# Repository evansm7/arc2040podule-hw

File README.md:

# RP2040-based Acorn Archimedes expansion card

22nd October 2021

This is a design for an expansion card (or "Podule" in Acorn-words) for the Acorn Archimedes computer.  Instead of the traditional EPROMs and 74-series logic, or PALs, this card uses the Raspberry Pi RP2040 microcontroller to interface directly to the expansion card bus.

This allows the functionality of the podule to be largely software-defined in the RP2040 firmware.

The card comprises 5V-3.3V buffering, the MCU, QSPI flash and crystal, and a USB micro-B device port for both programming the MCU and communicating with it when in action.

In conjunction with the [arc2040podule firmware](https://github.com/evansm7/arc2040podule), this podule provides a source of boot-time loaded Relocatable Modules (up to ~2MB, or ~8MB with large SPI flash fitted!) and a USB comms link with a host computer which can be used for file transfer, networking, etc.

**This is a work in progress!**  Board v1 was simply an experiment to prove the basic operation.  See below: v1 required extensive modifications to function, so _please do not build V1_.

Yes, it's sort of overkill to have two 133MHz processors providing IO for an 8MHz processor, but that's 2021 vs 1987 for you.  The RP2040 is ideal for this task because one core can be dedicated to the realtime bitbanging Arc bus cycles, with the other core dealing with comms and providing the peripheral model.

## Features

  * Raspberry Pi RP2040 microcontroller
  * Software-defined presentation to Archimedes
  * 4KB of expansion address space
  * Supports up to 8MB QSPI flash; almost all is free for ROM modules 
  * Supports open-collector IRQ and reset of the Archimedes
  * USB interface to a host computer (reflash, comms)
  * Debug blinky LED
  * SWD header
  * Reset button
  * BOOT button next to the Reset button for awkward, but possible, one-handed programming-reboot
  * Spare GPIO pins to a header
  * Micro-SD connector via SPI

## Principle of operation

The expansion card bus (and control signals) pass through 74AVLC164245 16-bit bus transceivers, which interface the 5V Arc to the 3.3V MCU.  The lower 8 bits of data are bidirectional, and the direction of the lower byte of the transceiver `IC3` is controlled by the `PR/nW` podule bus signal (called `PRNW` here).

The RP2040 polls the `/IORD` and `/IOWR` strobes, `/PS` podule select line, and address lines.  When a strobe falls, the RP2040 emulates the corresponding read or write cycle by presenting/capturing data on the `D[7:0]` data bus.

All address lines, `LA[13:2]`, are presented to the RP2040, permitting the full 16KB region to be decoded.

This podule only supports IOC cycles.  The `/IORQ` & `/IOGT` signals are not connected, due to lack of free GPIO pins.

Similarly, the RP2040 doesn't have enough GPIO pins to support a 16-bit data bus, so we deal with 8.

The good news is this podule is verified to perform synchronous (and slow) accesses correctly (v1 with hacks below, see notes).  Fast accesses have not been tested yet.

The RP2040 circuit is unremarkable and largely follows the RP design guide.  The BOOT signal is brought to a switch, which (on reset) conveniently brings the RP2040 up in USB MSD programming mode.

Browse the [schematic](doc/podule_2040_sch.pdf) and [board layout](doc/podule_2040_sch.pdf).

# Change log

## v2:

Changes from v1:

  * All points/v1 problems below have been resolved (but crystal still on bottom).
  * One more GPIO available (removed `NRST_I`).  GPIO header now brings out 4x GPIOs, 3.3V and ground.
  * Micro-SD footprint using GPIOs (corresponding to SPI1 pins).

**v2 has not been validated yet**  Boards are on their way.

## v1:

Requested changes (AKA a critique/lessons learned/mistakes in v1):

  * There's a fair bit of clown routing on v1 (late night, rushing to bundle this PCB off with another, regular excuses apply).  Clean routing.
   * Make net widths more consistent, e.g. some power nets change, and some are inconsistent either side of a component.
  * The QSPI routing is bad, and the decoupling is bad.  Fix both.
  * 74AVLC164245s are more easily available in TSSOP.  Change from SOP.
  * Add footprint for DNF pullup on flash `/CS`
  * 3.3V LDO is in an inconvenient/less common package.  Change for one of the cheap/plentiful packages (e.g. SOIC8)
  * Remove the `NRST_I` net input:  I found a software reset handshake is easier/more useful than polling for hardware reset.  This then frees a valuable single GPIO, for...
  * ...Add DNF SD footprint as an experimental option on 3x spare GPIOs (retain 0.1" header too).  Use newly-acquired spare GPIO for `/CS`.
  * Bring out USB Vbus to a link, or diode to 5V/LDO.  This would permit the board to be flashed while the host Arc is off, or unplugged.
  * Replace Y1 crystal footprint with a more common/available crystal.  (See notes.)
  * Move crystal to same side as MCU.
  * Decoupling:  Ensure 1x 0.1uF per power pin, even closer.  Caps closer to vias.  Add 0.1uF to QSPI flash.
  * Make address lines contiguous:  software _can_ juggle them, but it's a pain (and slows down the max cycle time).
  * _Crucially important_: Add 33Ω series termination on lines between the GPIO pins and the '245s.  See notes.
  * Wire both BOOT and RESET to a 4-pin header, for extension to 2 external buttons (e.g. outside the case of the Arc).

### Notes/observations on v1

I built the pictured prototype v1 with a 2MB QSPI flash, W25Q16JVSNIQ.  The flash doesn't work properly:  it only works slow, and I couldn't get 4-bit mode running.  Suspect decoupling & routing.

Ringing on the address lines hit a high voltage (~4V) and upset the RP2040.  This was a pain to find.  This manifest as USB stopping working while the Archimedes was powered on, yet working perfectly when it was off.  Adding 33Ω series termination on the address lines fixed this: add footprints on all control/data lines too (can always populate with 0Ω if it creates a problem).

The RP2040 design guide example uses a crystal with:
 
  * 27pF caps
  * 1K resistor
  * Crystal having 50 ohm ESR and 18pF load capacitance

The design guide says load cap should be (C1*C2)/(C1+C2)+parasitic, which (as caps are equal) simplifies to (C1/2)+parasitic.
Choose 5pF for parasitic and:  5+27/2 = 18.5, so choose 18pF crystal.

A similar worked example at: <https://suntsu.com/engineering-services/suntsu-application-notes/crystal-load-capacitance/>

Crystals in a 4-pin package (as used in v1) with 50 ohms and 18pF are uncommon.  For v1 I bodged on an 18pF 50ohm crystal (in wrong package -- Mouser 729-F91200084), and used 27pF caps.  Worked well.

Investigate more commonly-available packages, e.g. 4-pin but 3.2x2.5 instead of 5x3.2.

# Licence

This work is copyright 2021 Matt Evans, and is licenced under the Creative Commons CC BY-SA 3.0 license.

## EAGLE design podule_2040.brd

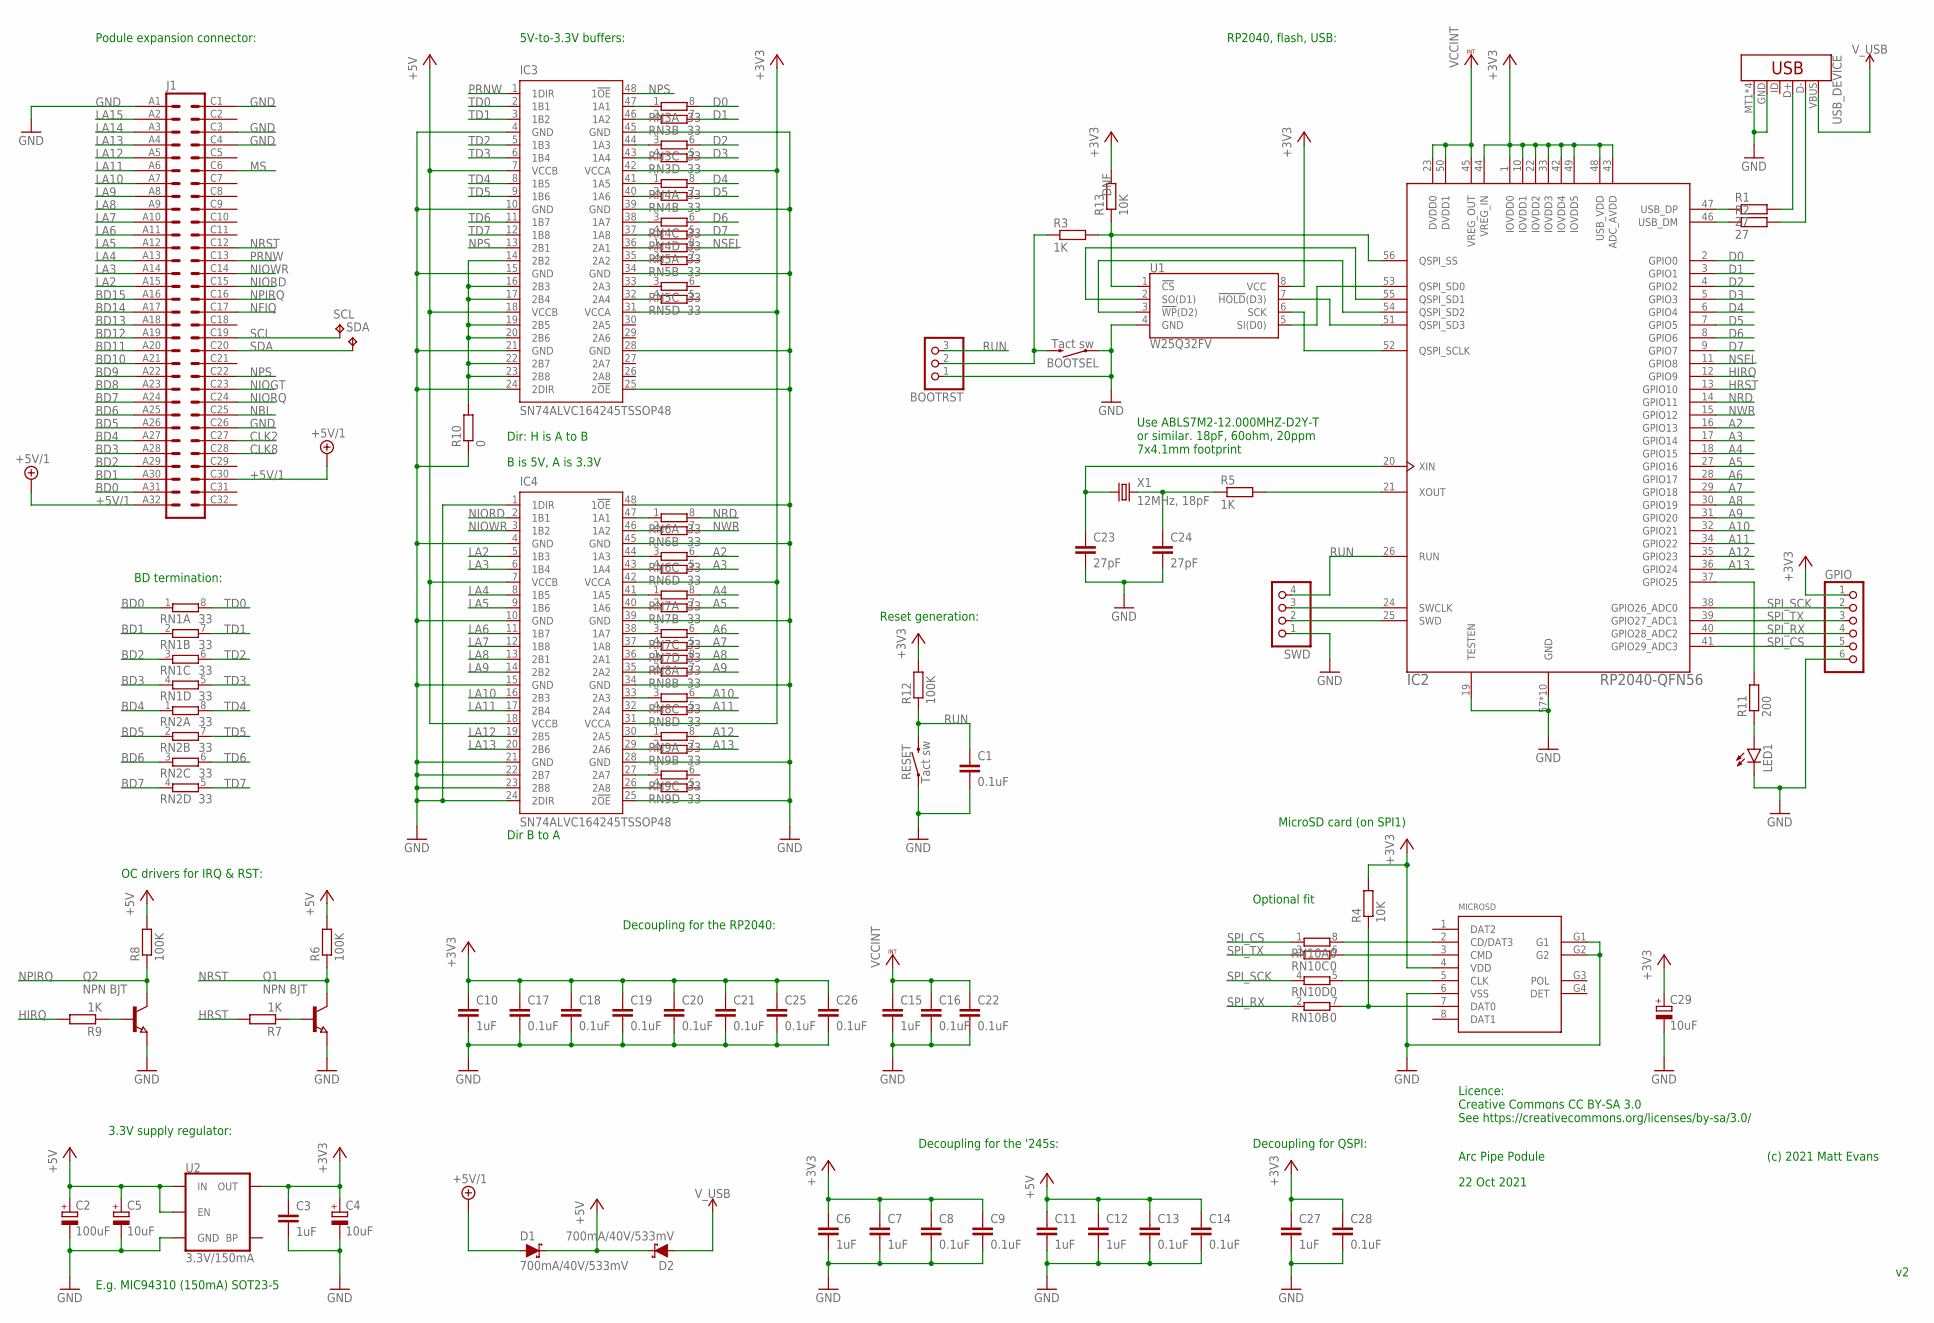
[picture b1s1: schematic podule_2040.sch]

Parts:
BOOTRST: PINHD-1X3; 1X03
BOOTSEL: Tact sw; TACTILE_SWITCH_SMD_5.2MM
C1, C8, C9, C13, C14, C16, C17, C18, C19, C20, C21, C22, C25, C26, C28: 0.1uF; C0603K
C2: 100uF; CT6032
C3, C6, C7, C10, C11, C12, C15, C27: 1uF; C0603K
C4, C5, C29: 10uF; A/3216-18W
C23, C24: 27pF; C0603K
D1, D2: 700mA/40V/533mV; SOT23-3
GPIO: PINHD-1X6; 1X06
IC2: RP2040-QFN56; RP2040-QFN-56
IC3, IC4: SN74ALVC164245TSSOP48; TSSOP48
J1: VG64SHORT; VG64KB-80MM
LED1: LEDCHIPLED_1206; CHIPLED_1206
MICROSD: MOLEX-USD-47309
Q1, Q2: NPN BJT; SOT23
R1, R2: 27; R0805
R3, R5, R7, R9: 1K; R0805
R4, R13: 10K; R0805
R6, R8, R12: 100K; R0805
R10: 0; R0603
R11: 200; R0805
RESET: Tact sw; TACTILE_SWITCH_SMD_5.2MM
RN1, RN2, RN3, RN4, RN5, RN6, RN7, RN8, RN9: 33; 0603-ARC
RN10: 0; 0603-ARC
SCL: TPTP15R; TP15R
SDA: TPTP15R; TP15R
SWD: PINHD-1X4; 1X04
U1: W25Q32FV; SOIC-8
U2: 3.3V/150mA; SOT23-5
USB_DEVICE: USB_MICRO-B_SMT; USB-MICROB
X1: 12MHz, 18pF; 7.5X5-2-PAD

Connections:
+3V3: C3.1, C4.+, C6.1, C7.1, C8.1, C9.1, C10.1, C17.1, C18.1, C19.1, C20.1, C21.1, C25.1, C26.1, C27.1, C28.1, C29.+, GPIO.1, IC2.1 (IOVDD0), IC2.10 (IOVDD1), IC2.22 (IOVDD2), IC2.33 (IOVDD3), IC2.42 (IOVDD4), IC2.43 (ADC_AVDD), IC2.44 (VREG_IN), IC2.48 (USB_VDD), IC2.49 (IOVDD5), IC3.31 (VCCA), IC3.42 (VCCA), IC4.31 (VCCA), IC4.42 (VCCA), MICROSD.4 (VDD), R4.2, R12.2, R13.2, U1.8 (VCC), U2.5 (OUT)
+5V: C2.+, C5.+, C11.1, C12.1, C13.1, C14.1, D1.3 (C), D2.3 (C), IC3.7 (VCCB), IC3.18 (VCCB), IC4.7 (VCCB), IC4.18 (VCCB), R6.2, R8.2, U2.1 (IN), U2.3 (EN)
+5V/1: D1.1 (A), J1.A32, J1.C30
A2: IC2.16 (GPIO13), RN6.6 (2)
A3: IC2.17 (GPIO14), RN6.5 (2)
A4: IC2.18 (GPIO15), RN7.8 (2)
A5: IC2.27 (GPIO16), RN7.7 (2)
A6: IC2.28 (GPIO17), RN7.6 (2)
A7: IC2.29 (GPIO18), RN7.5 (2)
A8: IC2.30 (GPIO19), RN8.8 (2)
A9: IC2.31 (GPIO20), RN8.7 (2)
A10: IC2.32 (GPIO21), RN8.6 (2)
A11: IC2.34 (GPIO22), RN8.5 (2)
A12: IC2.35 (GPIO23), RN9.8 (2)
A13: IC2.36 (GPIO24), RN9.7 (2)
BD0: J1.A31, RN1.1
BD1: J1.A30, RN1.2 (1)
BD2: J1.A29, RN1.3 (1)
BD3: J1.A28, RN1.4 (1)
BD4: J1.A27, RN2.1
BD5: J1.A26, RN2.2 (1)
BD6: J1.A25, RN2.3 (1)
BD7: J1.A24, RN2.4 (1)
BD8: J1.A23
BD9: J1.A22
BD10: J1.A21
BD11: J1.A20
BD12: J1.A19
BD13: J1.A18
BD14: J1.A17
BD15: J1.A16
CLK2: J1.C27
CLK8: J1.C28
D0: IC2.2 (GPIO0), RN3.8 (2)
D1: IC2.3 (GPIO1), RN3.7 (2)
D2: IC2.4 (GPIO2), RN3.6 (2)
D3: IC2.5 (GPIO3), RN3.5 (2)
D4: IC2.6 (GPIO4), RN4.8 (2)
D5: IC2.7 (GPIO5), RN4.7 (2)
D6: IC2.8 (GPIO6), RN4.6 (2)
D7: IC2.9 (GPIO7), RN4.5 (2)
GND: BOOTRST.1, BOOTSEL.1, BOOTSEL.2 (1), C1.2, C2.-, C3.2, C4.-, C5.-, C6.2, C7.2, C8.2, C9.2, C10.2, C11.2, C12.2, C13.2, C14.2, C15.2, C16.2, C17.2, C18.2, C19.2, C20.2, C21.2, C22.2, C23.2, C24.2, C25.2, C26.2, C27.2, C28.2, C29.-, GPIO.6, IC2.19 (TESTEN), IC2.57 (GND), IC2.58 (GND), IC2.59 (GND), IC2.60 (GND), IC2.61 (GND), IC2.62 (GND), IC2.63 (GND), IC2.64 (GND), IC2.65 (GND), IC2.66 (GND), IC3.4 (GND), IC3.10 (GND), IC3.15 (GND), IC3.21 (GND), IC3.24 (2DIR), IC3.25 (2!OE), IC3.28 (GND), IC3.34 (GND), IC3.39 (GND), IC3.45 (GND), IC4.1 (1DIR), IC4.4 (GND), IC4.10 (GND), IC4.15 (GND), IC4.21 (GND), IC4.22 (2B7), IC4.23 (2B8), IC4.24 (2DIR), IC4.25 (2!OE), IC4.28 (GND), IC4.34 (GND), IC4.39 (GND), IC4.45 (GND), IC4.48 (1!OE), J1.A1, J1.C1, J1.C3, J1.C4, J1.C26, LED1.C, MICROSD.6 (VSS), MICROSD.G1, MICROSD.G2, Q1.2 (E), Q2.2 (E), R10.1, RESET.1, RESET.2 (1), SWD.1, U1.4 (GND), U2.2 (GND), USB_DEVICE.GND, USB_DEVICE.MT1 (SHIELD), USB_DEVICE.MT2 (SHIELD), USB_DEVICE.P$1 (SHIELD), USB_DEVICE.P$2 (SHIELD)
HIRQ: IC2.12 (GPIO9), R9.2
HRST: IC2.13 (GPIO10), R7.2
LA2: IC4.5 (1B3), J1.A15
LA3: IC4.6 (1B4), J1.A14
LA4: IC4.8 (1B5), J1.A13
LA5: IC4.9 (1B6), J1.A12
LA6: IC4.11 (1B7), J1.A11
LA7: IC4.12 (1B8), J1.A10
LA8: IC4.13 (2B1), J1.A9
LA9: IC4.14 (2B2), J1.A8
LA10: IC4.16 (2B3), J1.A7
LA11: IC4.17 (2B4), J1.A6
LA12: IC4.19 (2B5), J1.A5
LA13: IC4.20 (2B6), J1.A4
LA14: J1.A3
LA15: J1.A2
MS: J1.C6
unnamed: IC2.47 (USB_DP), R1.1
unnamed: IC2.46 (USB_DM), R2.1
unnamed: R1.2, USB_DEVICE.D+
unnamed: R2.2, USB_DEVICE.D-
unnamed: IC2.52 (QSPI_SCLK), U1.6 (SCK)
unnamed: IC2.53 (QSPI_SD0), U1.5 (SI(D0))
unnamed: IC2.51 (QSPI_SD3), U1.7 (!HOLD!(D3))
unnamed: IC2.54 (QSPI_SD2), U1.3 (!WP!(D2))
unnamed: IC2.55 (QSPI_SD1), U1.2 (SO(D1))
unnamed: MICROSD.5 (CLK), RN10.5 (2)
unnamed: IC2.56 (QSPI_SS), R3.2, R13.1, U1.1 (!CS!)
unnamed: BOOTRST.2, BOOTSEL.3 (2), BOOTSEL.4 (2), R3.1
unnamed: IC2.21 (XOUT), R5.2
unnamed: MICROSD.2 (CD/DAT3), RN10.8 (2)
unnamed: IC2.25 (SWD), SWD.2
unnamed: IC2.24 (SWCLK), SWD.3
unnamed: C24.1, R5.1, X1.2
unnamed: Q1.1 (B), R7.1
unnamed: C23.1, IC2.20 (XIN), X1.1
unnamed: Q2.1 (B), R9.1
unnamed: IC3.47 (1A1), RN3.1
unnamed: IC3.14 (2B2), IC3.16 (2B3), IC3.17 (2B4), IC3.19 (2B5), IC3.20 (2B6), IC3.22 (2B7), IC3.23 (2B8), R10.2
unnamed: MICROSD.3 (CMD), RN10.6 (2)
unnamed: MICROSD.7 (DAT0), R4.1, RN10.7 (2)
unnamed: LED1.A, R11.1
unnamed: IC3.46 (1A2), RN3.2 (1)
unnamed: IC2.37 (GPIO25), R11.2
unnamed: IC3.32 (2A4), RN5.4 (1)
unnamed: IC3.44 (1A3), RN3.3 (1)
unnamed: IC3.43 (1A4), RN3.4 (1)
unnamed: IC3.40 (1A6), RN4.2 (1)
unnamed: IC3.41 (1A5), RN4.1
unnamed: IC3.38 (1A7), RN4.3 (1)
unnamed: IC3.37 (1A8), RN4.4 (1)
unnamed: IC3.36 (2A1), RN5.1
unnamed: IC3.35 (2A2), RN5.2 (1)
unnamed: IC3.33 (2A3), RN5.3 (1)
unnamed: IC4.47 (1A1), RN6.1
unnamed: IC4.46 (1A2), RN6.2 (1)
unnamed: IC4.44 (1A3), RN6.3 (1)
unnamed: IC4.43 (1A4), RN6.4 (1)
unnamed: IC4.41 (1A5), RN7.1
unnamed: IC4.40 (1A6), RN7.2 (1)
unnamed: IC4.38 (1A7), RN7.3 (1)
unnamed: IC4.37 (1A8), RN7.4 (1)
unnamed: IC4.36 (2A1), RN8.1
unnamed: IC4.35 (2A2), RN8.2 (1)
unnamed: IC4.33 (2A3), RN8.3 (1)
unnamed: IC4.32 (2A4), RN8.4 (1)
unnamed: IC4.30 (2A5), RN9.1
unnamed: IC4.29 (2A6), RN9.2 (1)
unnamed: IC4.27 (2A7), RN9.3 (1)
unnamed: IC4.26 (2A8), RN9.4 (1)
NBL: J1.C25
NFIQ: J1.C17
NIOGT: J1.C23
NIORD: IC4.2 (1B1), J1.C15
NIORQ: J1.C24
NIOWR: IC4.3 (1B2), J1.C14
NPIRQ: J1.C16, Q2.3 (C), R8.1
NPS: IC3.13 (2B1), IC3.48 (1!OE), J1.C22
NRD: IC2.14 (GPIO11), RN6.8 (2)
NRST: J1.C12, Q1.3 (C), R6.1
NSEL: IC2.11 (GPIO8), RN5.8 (2)
NWR: IC2.15 (GPIO12), RN6.7 (2)
PRNW: IC3.1 (1DIR), J1.C13
RUN: BOOTRST.3, C1.1, IC2.26 (RUN), R12.1, RESET.3 (2), RESET.4 (2), SWD.4
SCL: J1.C19, SCL.TP
SDA: J1.C20, SDA.TP
SPI_CS: GPIO.5, IC2.41 (GPIO29_ADC3), RN10.1
SPI_RX: GPIO.4, IC2.40 (GPIO28_ADC2), RN10.2 (1)
SPI_SCK: GPIO.2, IC2.38 (GPIO26_ADC0), RN10.4 (1)
SPI_TX: GPIO.3, IC2.39 (GPIO27_ADC1), RN10.3 (1)
TD0: IC3.2 (1B1), RN1.8 (2)
TD1: IC3.3 (1B2), RN1.7 (2)
TD2: IC3.5 (1B3), RN1.6 (2)
TD3: IC3.6 (1B4), RN1.5 (2)
TD4: IC3.8 (1B5), RN2.8 (2)
TD5: IC3.9 (1B6), RN2.7 (2)
TD6: IC3.11 (1B7), RN2.6 (2)
TD7: IC3.12 (1B8), RN2.5 (2)
VCCINT: C15.1, C16.1, C22.1, IC2.23 (DVDD0), IC2.45 (VREG_OUT), IC2.50 (DVDD1)
V_USB: D2.1 (A), USB_DEVICE.VBUS

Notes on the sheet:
B is 5V, A is 3.3V
Dir: H is A to B
Dir B to A
Podule expansion connector:
5V-to-3.3V buffers:
BD termination:
OC drivers for IRQ & RST:
3.3V supply regulator:
Decoupling for the '245s:
RP2040, flash, USB:
Arc Pipe Podule
(c) 2021 Matt Evans
22 Oct 2021
Licence: Creative Commons CC BY-SA 3.0 See https://creativecommons.org/licenses/by-sa/3.0/
E.g. MIC94310 (150mA) SOT23-5
Use ABLS7M2-12.000MHZ-D2Y-T or similar. 18pF, 60ohm, 20ppm 7x4.1mm footprint
Decoupling for the RP2040:
Reset generation:
Decoupling for QSPI:
Optional fit
MicroSD card (on SPI1)

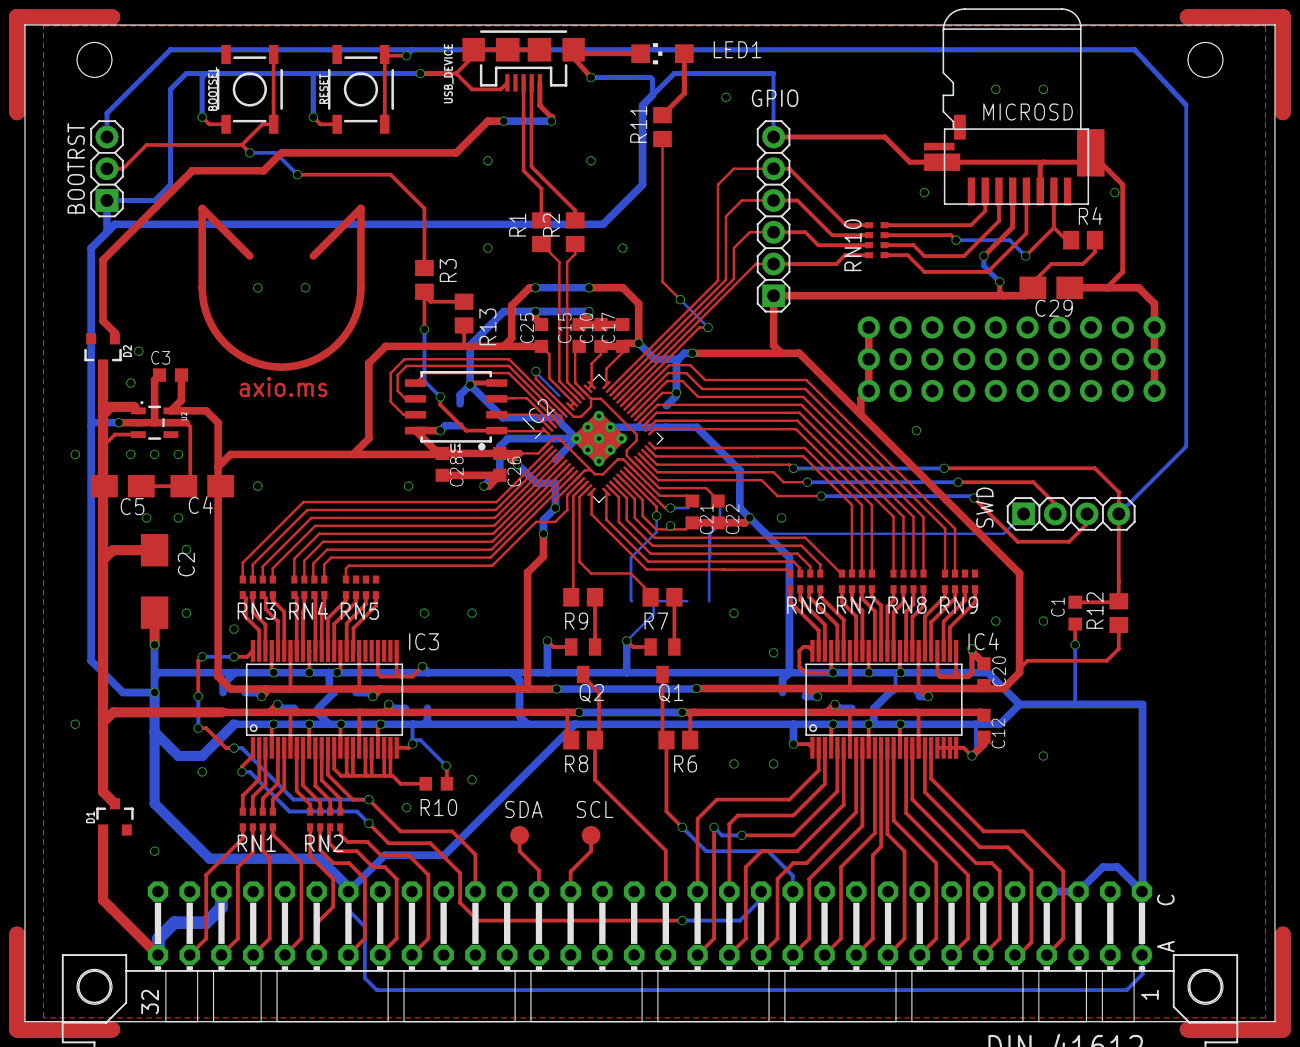
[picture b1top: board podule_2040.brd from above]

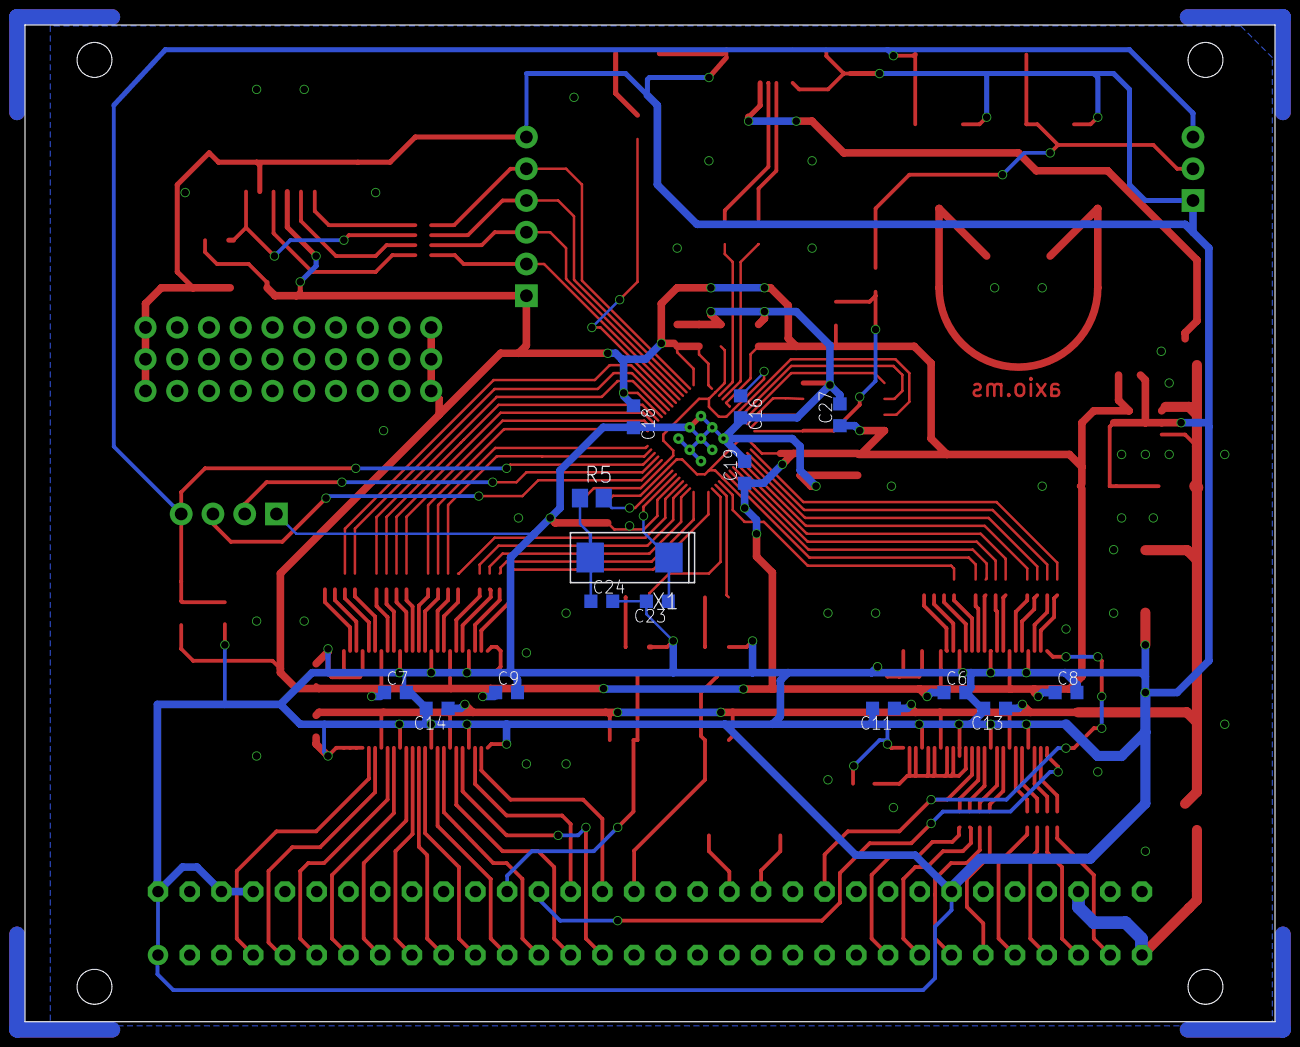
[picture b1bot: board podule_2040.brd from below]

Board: 2 copper layers, 100.0 x 79.8 mm, 73 parts (15 on the bottom side), 125 nets.

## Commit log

2021-10-06 Initial import
    ~v0.1: still needs final checks, DRC, beautification. May change USB socket. But, layout roughly there.
2021-10-06 Schematic & board V1: as used for prototype fab
2021-10-06 Add PDFs of v1 sch/brd
2021-10-06 Add README, board image
2021-10-06 Update README with link to firmware repo
2021-10-22 First commit of v2 design, for checking
    Changes include:
    - Shrink buffers to TSSOP
    - Term. resistor packs on internal signals
    - Removed N_RST input, freeing 4 GPIOs
    - GPIOs to header, prototyping area, and added uSD footprint/resistors
    - Moved QSPI closer, more decoupling, re-routed
2021-10-22 Tidy-ups for v2
    Not released yet: board looks good, work needed on README etc.
    Not fabricated yet.
2021-10-22 Update docs for v2 board

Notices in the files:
parts and their libraries:
SparkFun-Switches: Licensing: Creative Commons ShareAlike 4.0 International - https://creativecommons.org/licenses/by-sa/4.0
